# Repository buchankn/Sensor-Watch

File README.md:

Casio F-91W Step Counter
========================

This is a fork of Joey Castillo's Sensor-Watch (see https://github.com/joeycastillo/Sensor-Watch, and https://www.sensorwatch.net/). My changes to this fork is a work-in-progress.

My main goals are to:

* Add led 'side-lighting' to the right side of the LCD as well as the left
* Add a BMA400 accelerometer to the board for step counting, and perhaps experiment with wake-on-arm-lift, etc
* Add PAM8904E for a louder (and adjustable) piezo driver
* Remove USB, and add SWD Tag-Connect pads
* Add additional SWD pads on back of board (covered with tape when watch is assembled with the battery)

I replaced the 2 color led side light with 2 individual 0603 LEDs, so I could pick and choose each LED. Will it be better than the bi-color? We'll see... I chose not to go with an RGB LED, because I wanted LEDs on both sides of the display, and I couldn't spare 6 gpio for them. And I didn't want to connect multiple LEDs to one gpio, because it could exceed the max current for the gpio pin.

I also added a TPS610985 to the board, to ensure that the board always gets a stable 3V supply, and the voltage supply to the LEDs doesn't dip below the LED forward voltage. The GPIO pins have a higher rated current at 3V, so this also ensures that turning on the LEDs doesn't exceed the max GPIO current. Using a boost converter will decrease battery life, but it's still to be determined by how much. The TPS610985 is pretty amazingly efficient, so I'm hoping to still get decent battery life with it.

The PAM8904E should make the buzzer on the watch louder, and the voltage to the buzzer is adjustable by 3 levels, so there's a sort of volume control with it.

I added Tag-Connect pads to make programming the board easier, without having to mess with custom POGO pins and such. Also, the SWD pads on the back of the board will allow me to assemble the board with the LCD, but without the battery, and solder wires to the debug pads to debug the board with the LCD connected. This of course means there is no bootloader, and the board can only be programmed using SWD.

Kicad design files to be uploaded shortly, and I'll update the code in this repository to match all the changes/additions I made...

Prototype boards have been ordered from PCBWay! Crossing my fingers that I didn't miss anything :)

Things I plan on fixing/improving on version 2.0 of the PCB:

* I accidently placed a resistor in a "keep out" zone, where the white case touches the PCB. I'll have to cut the case a little for these boards to fit.
* Connect ENABLE_SECONDARY_POWER to a gpio pin, so that the transient response of the boost regulator can be improved during active mode (I'm thinking about the times I'm using PWM for the LEDs and buzzer).
* See if I can connect all three buttons to an RTC wake pin.

Here's a picture of the new pin assignemts I plan for version 2.0 of the PCB:

And pictures of version 1.0 of the PCB:

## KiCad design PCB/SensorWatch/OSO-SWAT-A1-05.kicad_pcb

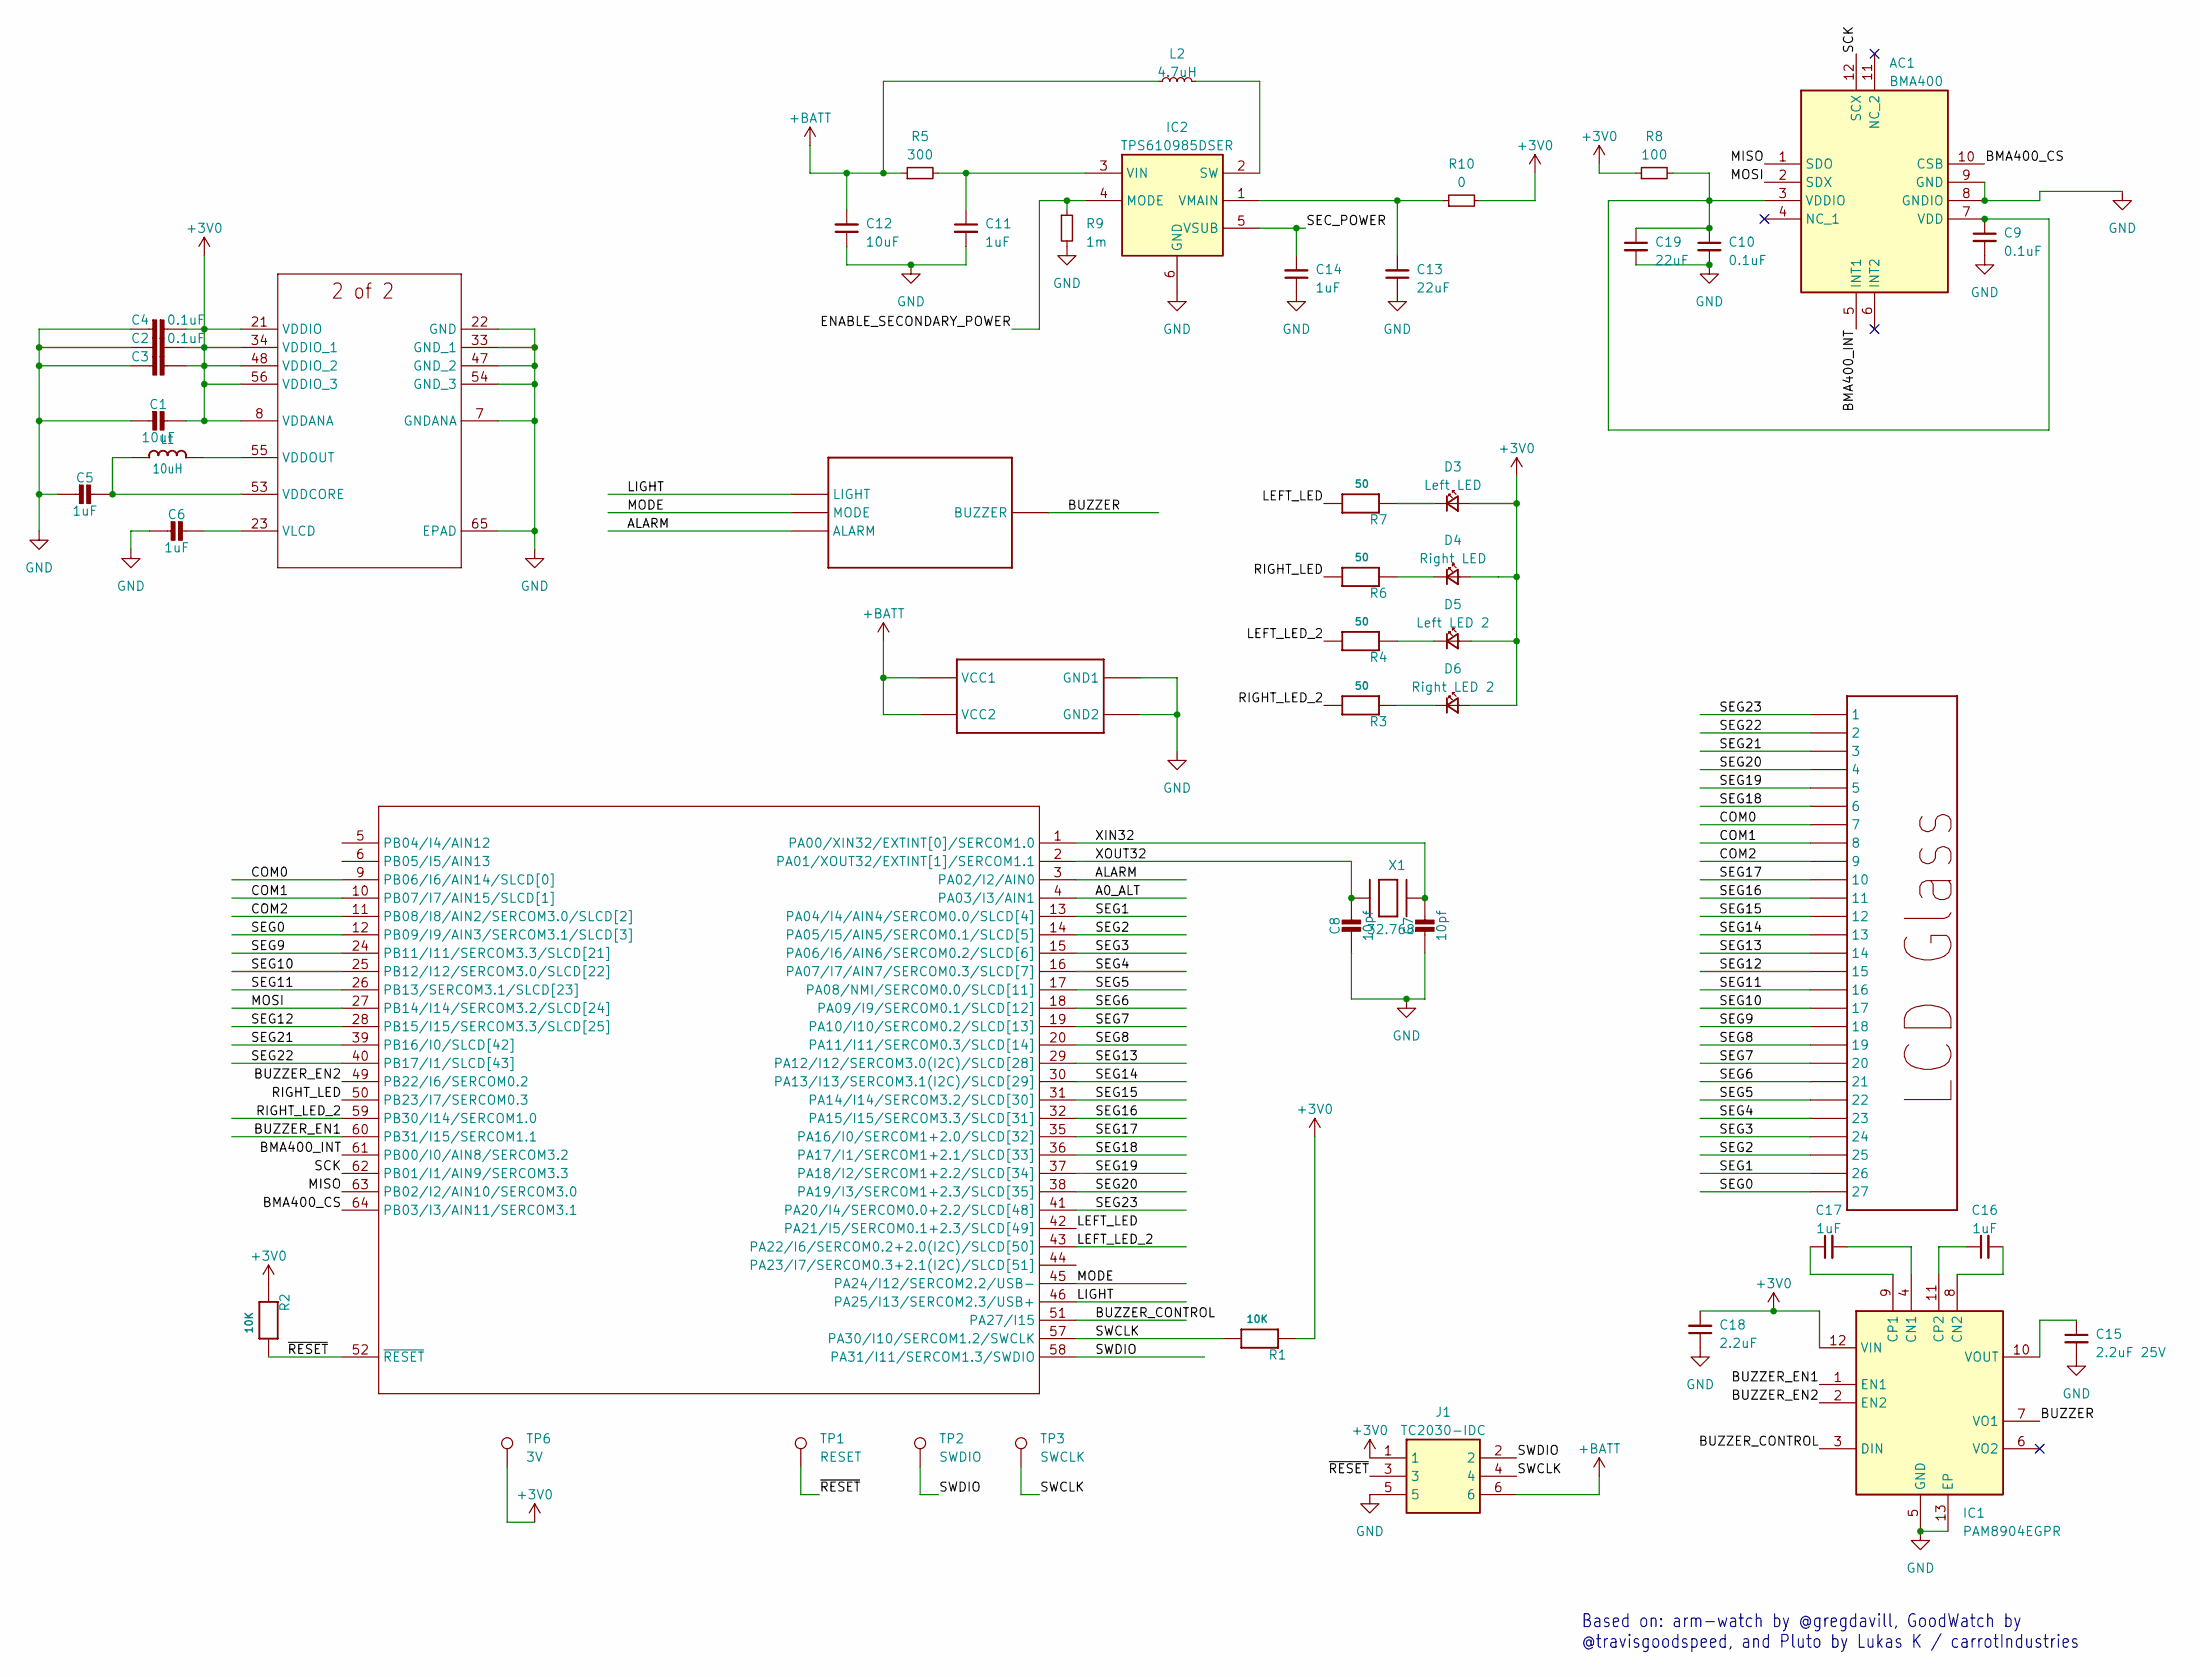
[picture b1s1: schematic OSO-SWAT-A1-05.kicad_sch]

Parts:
AC1: BMA400; BOSCH_LGA-12; Mouser2 Part Number 262-BMA400
C1, C12: 10uF; _0603MP
C2, C3, C4: 0.1uF; _0603MP
C5, C6: 1uF; _0603MP
C7, C8: 10pf; _0402MP
C9, C10: 0.1uF; _0402MP
C11, C14, C16, C17: 1uF; _0402MP
C13, C19: 22uF; _0402MP
C15: 2.2uF 25V; _0402MP
C18: 2.2uF; _0402MP
D3: Left LED; LED_APHD1608LZGCK; Part APHD1608LZGCK (GREEN)
D4: Right LED; LED_APHD1608LZGCK; Part APHD1608LZGCK (GREEN)
D5: Left LED 2; LED_APHD1608LZGCK; Part APHD1608LVBC/D (BLUE)
D6: Right LED 2; LED_APHD1608LZGCK; Part APHD1608LVBC/D (BLUE)
IC1: PAM8904EGPR; Mouser2 Part Number 621-PAM8904EGPR
IC2: TPS610985DSER; Manufacturer_Part_Number TPS610985DSER
J1: TC2030-IDC; TC2030IDC; Manufacturer_Part_Number TC2030-IDC
L1: 10uH; MICROBUILDER__0805MP
L2: 4.7uH; L_0805_2012Metric; Part Wurth 74438323047
O1: CASIO-F91W-OUTLINE-TAG-CONNECT
R1, R2: 10K; _0402MP
R3, R4, R6, R7: 50; _0402MP
R5: 300; _0402MP; Part Vishay Dale CRCW0402300RJNED
R8: 100; _0402MP; Part Vishay Dale CRCW0402300RJNED
R9: 1m; _0402MP
R10: 0; _0603MP; Part Vishay Dale CRCW0402300RJNED
TP1: RESET; TestPoint_Pad_D1.5mm
TP2: SWDIO; TestPoint_Pad_D1.5mm
TP3: SWCLK; TestPoint_Pad_D1.5mm
TP6: 3V; TestPoint_Pad_D1.5mm
U1: ATSAML22J18A-MUT; QFN64_9X9MC_MCH
X1: 32.768; XTAL3215

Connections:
+3V0: C1.1, C2.1, C3.1, C4.1, C18.2, D3.2 (A), D4.2 (A), D5.2 (A), D6.2 (A), IC1.12 (VIN), J1.1, R1.1, R2.1, R8.1, R10.2, TP6.1, U1.8 (VDDANA), U1.21 (VDDIO), U1.34 (VDDIO_1), U1.48 (VDDIO_2), U1.56 (VDDIO_3); also elsewhere on the board
+BATT: C12.2, J1.6, L2.1, O1.VCC1, O1.VCC2, R5.1
/A0_ALT: U1.4 (PA03/I3/AIN1)
/ALARM: O1.ALARM, U1.3 (PA02/I2/AIN0)
/BMA400_CS: AC1.10 (CSB), U1.64 (PB03/I3/AIN11/SERCOM3.1)
/BMA400_INT: AC1.5 (INT1), U1.61 (PB00/I0/AIN8/SERCOM3.2)
/BUZZER: IC1.7 (VO1), O1.BUZZER
/BUZZER_CONTROL: IC1.3 (DIN), U1.51 (PA27/I15)
/BUZZER_EN1: IC1.1 (EN1), U1.60 (PB31/I15/SERCOM1.1)
/BUZZER_EN2: IC1.2 (EN2), U1.49 (PB22/I6/SERCOM0.2)
/COM0: O1.7, U1.9 (PB06/I6/AIN14/SLCD[0])
/COM1: O1.8, U1.10 (PB07/I7/AIN15/SLCD[1])
/COM2: O1.9, U1.11 (PB08/I8/AIN2/SERCOM3.0/SLCD[2])
/ENABLE_SECONDARY_POWER: IC2.4 (MODE), R9.1
/LEFT_LED: R7.2, U1.42 (PA21/I5/SERCOM0.1+2.3/SLCD[49])
/LEFT_LED_2: R4.2, U1.43 (PA22/I6/SERCOM0.2+2.0(I2C)/SLCD[50])
/LIGHT: O1.LIGHT, U1.46 (PA25/I13/SERCOM2.3/USB+)
/MISO: AC1.1 (SDO), U1.63 (PB02/I2/AIN10/SERCOM3.0)
/MODE: O1.MODE, U1.45 (PA24/I12/SERCOM2.2/USB-)
/MOSI: AC1.2 (SDX), U1.27 (PB14/I14/SERCOM3.2/SLCD[24])
/RIGHT_LED: R6.2, U1.50 (PB23/I7/SERCOM0.3)
/RIGHT_LED_2: R3.2, U1.59 (PB30/I14/SERCOM1.0)
/SCK: AC1.12 (SCX), U1.62 (PB01/I1/AIN9/SERCOM3.3)
/SEC_POWER: C14.2, IC2.5 (VSUB)
/SEG0: O1.27, U1.12 (PB09/I9/AIN3/SERCOM3.1/SLCD[3])
/SEG1: O1.26, U1.13 (PA04/I4/AIN4/SERCOM0.0/SLCD[4])
/SEG2: O1.25, U1.14 (PA05/I5/AIN5/SERCOM0.1/SLCD[5])
/SEG3: O1.24, U1.15 (PA06/I6/AIN6/SERCOM0.2/SLCD[6])
/SEG4: O1.23, U1.16 (PA07/I7/AIN7/SERCOM0.3/SLCD[7])
/SEG5: O1.22, U1.17 (PA08/NMI/SERCOM0.0/SLCD[11])
/SEG6: O1.21, U1.18 (PA09/I9/SERCOM0.1/SLCD[12])
/SEG7: O1.20, U1.19 (PA10/I10/SERCOM0.2/SLCD[13])
/SEG8: O1.19, U1.20 (PA11/I11/SERCOM0.3/SLCD[14])
/SEG9: O1.18, U1.24 (PB11/I11/SERCOM3.3/SLCD[21])
/SEG10: O1.17, U1.25 (PB12/I12/SERCOM3.0/SLCD[22])
/SEG11: O1.16, U1.26 (PB13/SERCOM3.1/SLCD[23])
/SEG12: O1.15, U1.28 (PB15/I15/SERCOM3.3/SLCD[25])
/SEG13: O1.14, U1.29 (PA12/I12/SERCOM3.0(I2C)/SLCD[28])
/SEG14: O1.13, U1.30 (PA13/I13/SERCOM3.1(I2C)/SLCD[29])
/SEG15: O1.12, U1.31 (PA14/I14/SERCOM3.2/SLCD[30])
/SEG16: O1.11, U1.32 (PA15/I15/SERCOM3.3/SLCD[31])
/SEG17: O1.10, U1.35 (PA16/I0/SERCOM1+2.0/SLCD[32])
/SEG18: O1.6, U1.36 (PA17/I1/SERCOM1+2.1/SLCD[33])
/SEG19: O1.5, U1.37 (PA18/I2/SERCOM1+2.2/SLCD[34])
/SEG20: O1.4, U1.38 (PA19/I3/SERCOM1+2.3/SLCD[35])
/SEG21: O1.3, U1.39 (PB16/I0/SLCD[42])
/SEG22: O1.2, U1.40 (PB17/I1/SLCD[43])
/SEG23: O1.1, U1.41 (PA20/I4/SERCOM0.0+2.2/SLCD[48])
/SWCLK: J1.4, R1.2, TP3.1, U1.57 (PA30/I10/SERCOM1.2/SWCLK)
/SWDIO: J1.2, TP2.1, U1.58 (PA31/I11/SERCOM1.3/SWDIO)
/XIN32: C7.1, U1.1 (PA00/XIN32/EXTINT[0]/SERCOM1.0), X1.P$1
/XOUT32: C8.1, U1.2 (PA01/XOUT32/EXTINT[1]/SERCOM1.1), X1.P$2
/~RESET: J1.3, R2.2, TP1.1, U1.52 (~RESET)
GND: AC1.8 (GNDIO), AC1.9 (GND), C1.2, C2.2, C3.2, C4.2, C5.2, C6.2, C7.2, C8.2, C9.2, C10.2, C11.2, C12.1, C13.1, C14.1, C15.2, C18.1, C19.2, IC1.5 (GND), IC1.13 (EP), IC2.6 (GND), J1.5, O1.GND1, O1.GND2, R9.2, U1.7 (GNDANA), U1.22 (GND), U1.33 (GND_1), U1.47 (GND_2), U1.54 (GND_3), U1.65 (EPAD)
unnamed: AC1.3 (VDDIO), AC1.7 (VDD), C9.1, C10.1, C19.1, R8.2
unnamed: D3.1 (K), R7.1
unnamed: D4.1 (K), R6.1
unnamed: D5.1 (K), R4.1
unnamed: D6.1 (K), R3.1
unnamed: C17.2, IC1.4 (CN1)
unnamed: C16.2, IC1.8 (CN2)
unnamed: C17.1, IC1.9 (CP1)
unnamed: C16.1, IC1.11 (CP2)
unnamed: C15.1, IC1.10 (VOUT)
unnamed: IC2.2 (SW), L2.2
unnamed: C11.1, IC2.3 (VIN), R5.2
unnamed 66: C13.2, IC2.1 (VMAIN), R10.1; also elsewhere on the board
unnamed: C5.1, L1.1, U1.53 (VDDCORE)
unnamed: L1.2, U1.55 (VDDOUT)
unnamed: C6.1, U1.23 (VLCD)

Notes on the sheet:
Based on: arm-watch by @gregdavill, GoodWatch by @travisgoodspeed, and Pluto by Lukas K / carrotIndustries

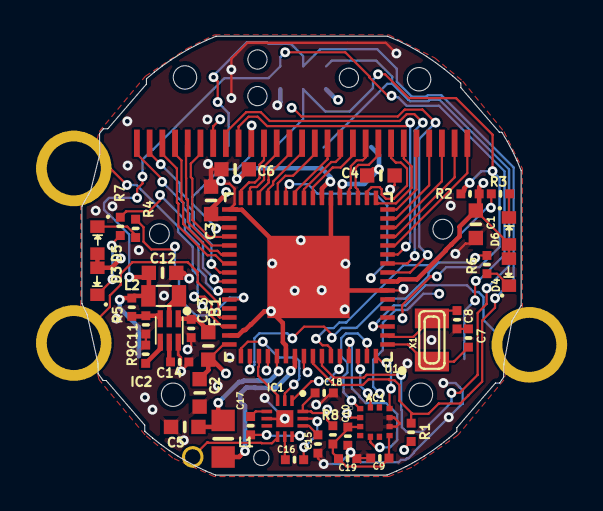
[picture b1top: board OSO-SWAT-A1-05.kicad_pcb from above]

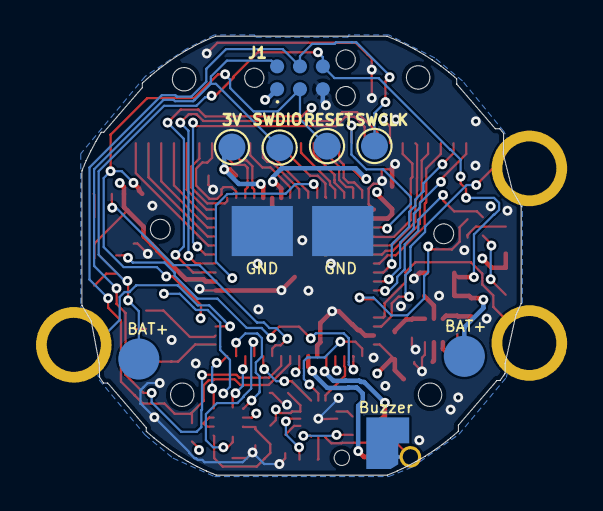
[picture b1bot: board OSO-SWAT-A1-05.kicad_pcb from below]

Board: 4 copper layers, 24.4 x 24.4 mm, 46 parts (5 on the bottom side), 69 nets.

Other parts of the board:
FB1: FerriteBead_Small; _0603MP

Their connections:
+3V0: FB1.2; also elsewhere on the board
unnamed 66: FB1.1; also elsewhere on the board

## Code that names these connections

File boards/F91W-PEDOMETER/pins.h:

#ifndef PINS_H_INCLUDED
#define PINS_H_INCLUDED

// Buttons
#define BTN_ALARM GPIO(GPIO_PORTA, 2)
#define WATCH_BTN_ALARM_EIC_CHANNEL 2
#define BTN_LIGHT GPIO(GPIO_PORTA, 25)
#define WATCH_BTN_LIGHT_EIC_CHANNEL 13
#define BTN_MODE GPIO(GPIO_PORTA, 24)
#define WATCH_BTN_MODE_EIC_CHANNEL 12

// Buzzer
#define BUZZER GPIO(GPIO_PORTA, 27)
#define WATCH_BUZZER_TCC_PINMUX PINMUX_PA27F_TCC0_WO5
#define WATCH_BUZZER_TCC_CHANNEL 1

#define BUZZER_EN_1 GPIO(GPIO_PORTB, 31)
#define BUZZER_EN_2 GPIO(GPIO_PORTB, 22)

// LEDs
#define WATCH_INVERT_LED_POLARITY
#define WATCH_LED_1_TCC_CHANNEL 3
#define WATCH_LED_2_TCC_CHANNEL 0

#define LEFT_LED_1 GPIO(GPIO_PORTA, 21)
#define WATCH_LEFT_LED_1_TCC_PINMUX PINMUX_PA21F_TCC0_WO7

#define LEFT_LED_2 GPIO(GPIO_PORTA, 22)
#define WATCH_LEFT_LED_2_TCC_PINMUX PINMUX_PA22F_TCC0_WO4

#define RIGHT_LED_1 GPIO(GPIO_PORTB, 23)
#define WATCH_RIGHT_LED_1_TCC_PINMUX PINMUX_PB23F_TCC0_WO3

#define RIGHT_LED_2 GPIO(GPIO_PORTB, 30)
#define WATCH_RIGHT_LED_2_TCC_PINMUX PINMUX_PB30E_TCC0_WO0


// Segment LCD
#define SLCD0 GPIO(GPIO_PORTB, 6)   // COM0
#define SLCD1 GPIO(GPIO_PORTB, 7)   // COM1
#define SLCD2 GPIO(GPIO_PORTB, 8)   // COM2
#define SLCD3 GPIO(GPIO_PORTB, 9)   // SEG0
#define SLCD4 GPIO(GPIO_PORTA, 4)   // SEG1
#define SLCD5 GPIO(GPIO_PORTA, 5)   // SEG2
#define SLCD6 GPIO(GPIO_PORTA, 6)   // SEG3
#define SLCD7 GPIO(GPIO_PORTA, 7)   // SEG4
#define SLCD8 GPIO(GPIO_PORTA, 8)  // SEG5
#define SLCD9 GPIO(GPIO_PORTA, 9)  // SEG6
#define SLCD10 GPIO(GPIO_PORTA, 10) // SEG7
#define SLCD11 GPIO(GPIO_PORTA, 11) // SEG8
#define SLCD12 GPIO(GPIO_PORTB, 11) // SEG9
#define SLCD13 GPIO(GPIO_PORTB, 12) // SEG10
#define SLCD14 GPIO(GPIO_PORTB, 13) // SEG11
#define SLCD15 GPIO(GPIO_PORTB, 15) // SEG12
#define SLCD16 GPIO(GPIO_PORTA, 12) // SEG13
#define SLCD17 GPIO(GPIO_PORTA, 13) // SEG14
#define SLCD18 GPIO(GPIO_PORTA, 14) // SEG15
#define SLCD19 GPIO(GPIO_PORTA, 15) // SEG16
#define SLCD20 GPIO(GPIO_PORTA, 16) // SEG17
#define SLCD21 GPIO(GPIO_PORTA, 17) // SEG18
#define SLCD22 GPIO(GPIO_PORTA, 18) // SEG19
#define SLCD23 GPIO(GPIO_PORTA, 19) // SEG20
#define SLCD24 GPIO(GPIO_PORTB, 16) // SEG21
#define SLCD25 GPIO(GPIO_PORTB, 17) // SEG22
#define SLCD26 GPIO(GPIO_PORTA, 20) // SEG23

// This board uses a slightly different pin mapping from the standard watch, and it's not enough to
// just declare the pins. We also have to set the LCD Pin Enable register with the SLCD pins we're
// using. These numbers are not port/pin numbers, but the "SLCD/LP[x]" numbers in the pinmux table.
// If not defined in pins.h, the LCD driver will fall back to the pin mapping in hpl_slcd_config.h.
// LPENL is for pins SLCD/LP[0..31].
#define CONF_SLCD_LPENL (\
        (uint32_t)1 <<  0 | \
        (uint32_t)1 <<  1 | \
        (uint32_t)1 <<  2 | \
        (uint32_t)1 <<  3 | \
        (uint32_t)1 <<  4 | \
        (uint32_t)1 <<  5 | \
        (uint32_t)1 <<  6 | \
        (uint32_t)1 <<  7 | \
        (uint32_t)1 << 11 | \
        (uint32_t)1 << 12 | \
        (uint32_t)1 << 13 | \
        (uint32_t)1 << 14 | \
        (uint32_t)1 << 21 | \
        (uint32_t)1 << 22 | \
        (uint32_t)1 << 23 | \
        (uint32_t)1 << 25 | \
        (uint32_t)1 << 28 | \
        (uint32_t)1 << 29 | \
        (uint32_t)1 << 30 | \
        (uint32_t)1 << 31 | 0)
// LPENH is for pins SLCD/LP[32..51], where bit 0 represents pin 32.
#define CONF_SLCD_LPENH (\
        (uint32_t)1 << (32 - 32) | \
        (uint32_t)1 << (33 - 32) | \
        (uint32_t)1 << (34 - 32) | \
        (uint32_t)1 << (35 - 32) | \
        (uint32_t)1 << (42 - 32) | \
        (uint32_t)1 << (43 - 32) | \
        (uint32_t)1 << (48 - 32) | 0)


// 9-pin connector
#define A0 GPIO(GPIO_PORTB, 4)
#define WATCH_A0_EIC_CHANNEL 4
#define A1 GPIO(GPIO_PORTB, 1)
#define WATCH_A1_EIC_CHANNEL 1
#define A2 GPIO(GPIO_PORTB, 2)
#define WATCH_A2_EIC_CHANNEL 2
#define A3 GPIO(GPIO_PORTB, 3)
#define WATCH_A3_EIC_CHANNEL 3
#define A4 GPIO(GPIO_PORTB, 0)
#define WATCH_A4_EIC_CHANNEL 0
#define SDA GPIO(GPIO_PORTB, 30)
#define SCL GPIO(GPIO_PORTB, 31)

// aliases for as A3/A4; these were mentioned as D0/D1 in early documentation.
#define D0 GPIO(GPIO_PORTB, 3)
#define D1 GPIO(GPIO_PORTB, 0)

#endif // PINS_H_INCLUDED

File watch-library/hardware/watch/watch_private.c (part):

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    // The buzzer will set the period depending on the tone it wants to play, but we have to set some period here to
    // get the LED working. Almost any period will do, tho it should be below 20000 (i.e. 50 Hz) to avoid flickering.
    hri_tcc_write_PER_reg(TCC0, 1024);
    // Set the duty cycle of all pins to 0: LED's off, buzzer not buzzing.
    hri_tcc_write_CC_reg(TCC0, WATCH_BUZZER_TCC_CHANNEL, 0);

#if BOARD != F91W-PEDOMETER
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    gpio_set_pin_direction(LEFT_LED_1, GPIO_DIRECTION_OUT);
    gpio_set_pin_function(LEFT_LED_1, WATCH_LEFT_LED_1_TCC_PINMUX);

    gpio_set_pin_direction(LEFT_LED_2, GPIO_DIRECTION_OUT);
    gpio_set_pin_function(LEFT_LED_2, WATCH_LEFT_LED_2_TCC_PINMUX);

    gpio_set_pin_direction(RIGHT_LED_1, GPIO_DIRECTION_OUT);
    gpio_set_pin_function(RIGHT_LED_1, WATCH_RIGHT_LED_1_TCC_PINMUX);

    gpio_set_pin_direction(RIGHT_LED_2, GPIO_DIRECTION_OUT);
    gpio_set_pin_function(RIGHT_LED_2, WATCH_RIGHT_LED_2_TCC_PINMUX);
#endif
}

void _watch_disable_tcc(void) {
    // disable all PWM pins
    gpio_set_pin_direction(BUZZER, GPIO_DIRECTION_OFF);
    gpio_set_pin_function(BUZZER, GPIO_PIN_FUNCTION_OFF);
#if BOARD != F91W-PEDOMETER
    gpio_set_pin_direction(RED, GPIO_DIRECTION_OFF);
    gpio_set_pin_function(RED, GPIO_PIN_FUNCTION_OFF);
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#else
    gpio_set_pin_direction(LEFT_LED_1, GPIO_DIRECTION_OFF);
    gpio_set_pin_function(LEFT_LED_1, GPIO_PIN_FUNCTION_OFF);
    gpio_set_pin_direction(LEFT_LED_2, GPIO_DIRECTION_OFF);
    gpio_set_pin_function(LEFT_LED_2, GPIO_PIN_FUNCTION_OFF);
    gpio_set_pin_direction(RIGHT_LED_1, GPIO_DIRECTION_OFF);
    gpio_set_pin_function(RIGHT_LED_1, GPIO_PIN_FUNCTION_OFF);
    gpio_set_pin_direction(RIGHT_LED_2, GPIO_DIRECTION_OFF);
    gpio_set_pin_function(RIGHT_LED_2, GPIO_PIN_FUNCTION_OFF);
#endif

    // disable the TCC
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    hri_mclk_set_APBBMASK_USB_bit(MCLK);

    // USB Pin Init
    gpio_set_pin_direction(PIN_PA24, GPIO_DIRECTION_OUT);
    gpio_set_pin_level(PIN_PA24, false);
    gpio_set_pin_pull_mode(PIN_PA24, GPIO_PULL_OFF);
    gpio_set_pin_direction(PIN_PA25, GPIO_DIRECTION_OUT);
    gpio_set_pin_level(PIN_PA25, false);
    gpio_set_pin_pull_mode(PIN_PA25, GPIO_PULL_OFF);

    gpio_set_pin_function(PIN_PA24, PINMUX_PA24G_USB_DM);
    gpio_set_pin_function(PIN_PA25, PINMUX_PA25G_USB_DP);

    // before we init TinyUSB, we are going to need a periodic callback to handle TinyUSB tasks.
    // TC2 and TC3 are reserved for devices on the 9-pin connector, so let's use TC0.
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
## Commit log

2023-05-18 Describe some of my sensor watch changes
2023-05-18 Add PCB pictures
2023-05-18 remove original pictures
2023-05-18 Add kicad project
2023-05-19 link without bootloader
2023-05-19 Change start address to 0x0
2023-05-20 Add new pins.h for F91W-PEDOMETER, and start making changes for extra LEDs (in-work)
2023-05-20 More LED fixes
2023-05-20 Set up LCD pins
2023-05-21 Add picture of new pin assignments for PCB version 2.0

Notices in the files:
watch-library/hardware/watch/watch_private.c:
MIT License
Copyright (c) 2020 Joey Castillo
The MIT License (MIT)
Copyright (c) 2019 Ha Thach (tinyusb.org)
